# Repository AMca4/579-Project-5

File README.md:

# EE579 ADVANCED MICROCONTROLLER PROJECT
## General project instructions and objectives
The following is essentially what we wrre tasked to do.

Build a vehicle capable of playing a game of skittles in the corridor outside RC6.41.
Two teams' vehicles will compete simultaneously, with a single set of 2 black metal “skittles” placed between 6 and 10 metres from both vehicles, and both vehicles beginning adjacent to each other. The skittles will consist of two tin soup cans soldered end to end and painted.

You will be given a model car to modify. You are expected to retro-fit this vehicle to operate autonomously, without altering the chassis (in particular, the wheel positions or bearings) or the drive train of the vehicle. Teams will be given two runs, alongside another vehicle. Runs will be 2 minutes long. During the heat, no team member will be permitted beyond the start line. Teams will score the number of complete seconds until they knock over the skittle, or two minutes per skittle if they do not knock over the skittle. The object is to get the lowest score in a round, and the lowest score from the two rounds will be counted. The top four teams will compete in a semi-final and the final two in the final.

In addition to two black skittles there will be a white skittle. Knocking over the white skittle will result in disqualification from the round.
+ Teams will see the position of the skittles one minute prior to the start of a round.
- The vehicle must operate autonomously. No external control may be given to the vehicle after it has been started.
- For the purposes of adjudicating a tie, the vehicle displacement from the start line at the end of the round will be measured, with longer distances scoring higher.

Marks for the project will be calculated on a group basis. The design and construction of the device will be marked out of 300. The team scoring the shortest time (or greatest displacement, should no team finish), will be given at additional 30 bonus marks. The group coming second will get 15 additional marks.

The design is unconstrained, except that your design may not run a general purpose operating system, such as Linux. Passive components can be requested from the workshop. Other components may be requested but a case may need to be made.

A Technical Documentation File must be produced for the design. This file must include:
- The specification of the design.
- Description of the hardware including circuit diagram and test points/instructions.
- Description of the software including a functional description.
- Usage instructions

The TDF is not a description of the construction of the project, but a description of the end product. A key assessment criteria of the TDF will be how easy it would be, using the TDF, to make a modification or extension to the design. It is expected that the TDF will be in the order of 25 to 30 pages, including diagrams.

In addition to the Technical Document File, a Policies and Procedures Document (PPD) must be produced documenting your group working practices, and in particular code versioning and review, and also measures taken during the design and construction phase to increase resilience to delays due to illness or other unforeseen circumstances. The PPD is expected to be in the order of one or two pages.

A descriptive report on the project is not required. However, the log books of each project member must be returned with the Technical Documentation File and it is expected that these log books will describe the design and debugging process.

By default, the group mark will be divided equally between all group members. However, group members may ask for a different proportional assignment of marks between group members at the time the project is submitted. It is up to group members themselves to make decisions regarding which group member should undertake which part of the design. The project is to be demonstrated during the exam diet. The Technical Documentation File must be submitted on or before the Monday of the week following the demo. The mark allocated to each student will be considered to be a percentage, 70% of which will go towards the final course mark. The remaining 30% of the final mark will come from the log book and assignments.

Room RC6.23 is allocated to the class on Friday for constructing and testing the hardware. Safety regulations require that more than one person be present in the room when any work is carried out - attending as a group satisfies this requirement.
## Setup instructions
We have used VS code for building this project. The following are the instructions for setting up the environment, if you wish to alter the code and flash it to the ESP32.
### Windows setup:
- Step 1: Download the latest version of [Python](https://www.python.org/downloads/) and [Git](https://git-scm.com/download/win) 
- Step 2: Download Espressif's Toolchain [here](https://docs.espressif.com/projects/esp-idf/en/latest/esp32/get-started/windows-setup.html).
- Step 3: Make sure to open the installer with administrator rights. On the third screen, ***don't click on next before the scanning is complete!***. If there are no warnings you may procceed to the next step by clicking next. If you notice warnings, click on apply fixes and grant administrator rights on the pop-up screen. You may then proceed to the next step by clicking on next.
- Step 4: You may select to Download ESP-IDF or Use an existing ESP-IDF directory if you already have an installation on the ESP-IDF Tools.
- Step 5: ***This is a very crucial step!*** Make sure you make a note of the directory it wants to install to and select any of the above. Our recommendation is to select the latest release from (release branch - git clone).
- Step 6: Specify where you would like the ESP-IDF Tools to be installed and **make a note of it!**
- Step 7: You may select any of the options but we recommend you go for the full installation, always making sure to select the appropriate drivers for your own board.
- Step 8: In the *Ready to Install* screen verify all your choices by clicking Install. At this stage it's good to once more make a note of the location for the *ESP-IDF* and the *IDF_TOOLS_PATH*.
- Step 9: You'll now get a couple of pop-ups for granting administrator rights and another one for installing the drivers. Make sure to grant all of these. You can now let the installer download and install the ESP-IDF.
- Step 10: Download [VS code](https://code.visualstudio.com/download) and install using the default options.
- Step 11: Once the setup is complete, open VS code and click on Crtl+Shift+X navigate to the extentions tab. You can also find it on the left hand-side of VS Code. In the search bar type in ESP-IDF and install it.
- Step 12: You can now press Crtl+Shift+P (or navigate to the top of VS code and click on the search bar & click on *Show and Run Commands*) and type in *Configure ESP-IDF Extention*. Give it a second to load and then you'll be greeted with a welcome screen.
- Step 13: Choose *USE EXISTING SETUP* and then your installation should appear. Clicking on it, will install the necessary libraries for VS code to communicate with the ESP-IDF tools and once instructed you may close the window. You can skip to step 15.
- Step 14: If your installation doesn't appear, choose *Search ESP-IDF in system* and select the download server (*github if you followed our instructions above*) and *Find ESP-IDF in your system* from the dropdown. Now specify the locations for the *ESP-IDF* and the *IDF_TOOLS_PATH* from step 8 and click on install. Wait for it to finish and once instructed you may close the window.
- Step 15: Congratulations! You have successfully set-up *ESP-IDF* in your system!

### MacOS Setup:
- Follow the steps listed [here](https://docs.espressif.com/projects/esp-idf/en/stable/esp32/get-started/linux-macos-setup.html).

### Linux Setup:
- Follow the steps listed [here](https://docs.espressif.com/projects/esp-idf/en/stable/esp32/get-started/linux-macos-setup.html).

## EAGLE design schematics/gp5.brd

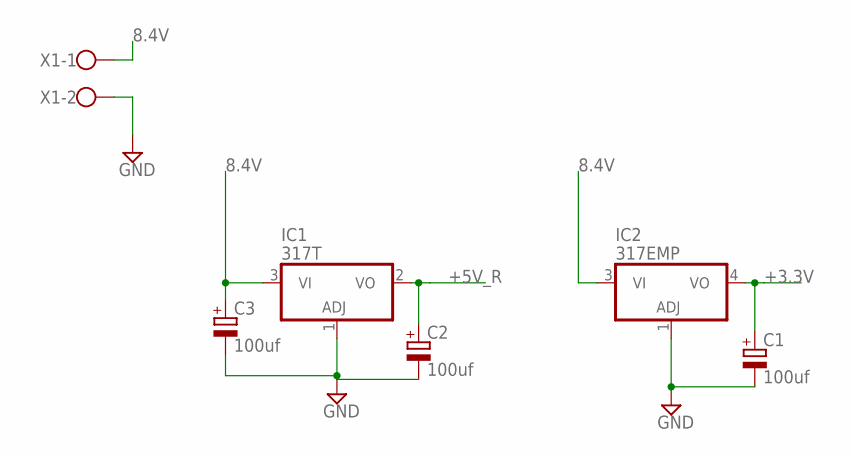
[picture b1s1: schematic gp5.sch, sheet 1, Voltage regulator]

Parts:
C1, C2, C3: 100uf; B45181B
IC1: 317T; TO220H
IC2: 317EMP; SOT223
X1: W237-102

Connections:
8.4V: C3.+, IC1.3 (VI), IC2.3 (VI), X1.1
+3.3V: C1.+, IC2.4 (VO); also elsewhere on the board
+5V_R: C2.+, IC1.2 (VO); also elsewhere on the board
GND: C1.-, C2.-, C3.-, IC1.1 (ADJ), IC2.1 (ADJ), X1.2; also elsewhere on the board

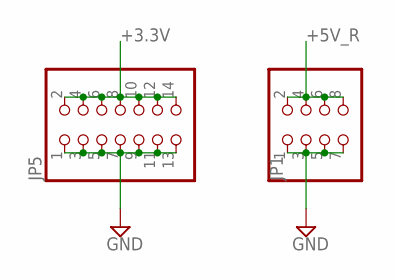
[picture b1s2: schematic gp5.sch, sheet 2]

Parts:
JP1: PINHD-2X4; 2X04
JP5: PINHD-2X7; 2X07

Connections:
+3.3V: JP5.2, JP5.4, JP5.6, JP5.8, JP5.10, JP5.12, JP5.14; also elsewhere on the board
+5V_R: JP1.2, JP1.4, JP1.6, JP1.8; also elsewhere on the board
GND: JP1.1, JP1.3, JP1.5, JP1.7, JP5.1, JP5.3, JP5.5, JP5.7, JP5.9, JP5.11, JP5.13; also elsewhere on the board

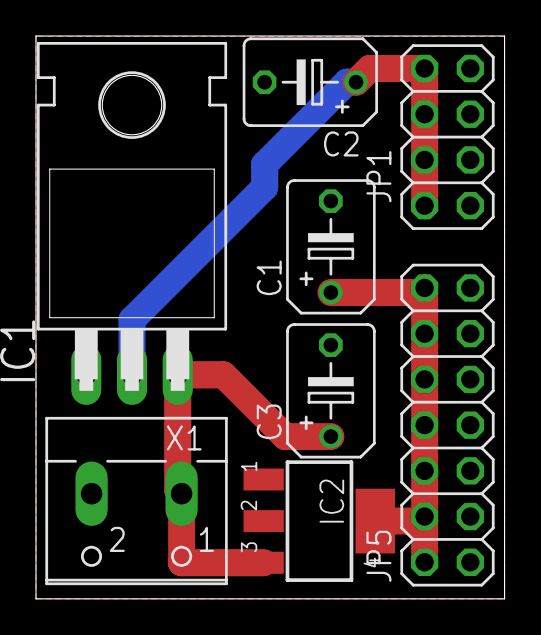
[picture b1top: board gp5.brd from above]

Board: 2 copper layers, 26.0 x 31.3 mm, 8 parts (0 on the bottom side), 4 nets.

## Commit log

2024-01-17 Update README.md
    Update READMe
2024-01-17 Update README.md
    Restructured READMe file
2024-01-25 Added .gitignore file
2024-01-27 Update README.md to include windows setup instructions
2024-01-27 Update README.md to use bullet points.
2024-01-29 Update README.md to include general instructions and objectives.
2024-01-29 Update README.md to fix bullet points
2024-01-29 Update README.md to finally fix the bullet points
2024-01-31 Delete skittles_project.code-workspace
    will re-upload
2024-01-31 Delete skittles.code.code-workspace
    will re-upload
2024-01-31 re-upload finalised ultrasonic code
2024-02-06 Putting the ultrasonic code into a folder
2024-02-06 Putting the ultrasonic folder up
2024-02-06 Update README.md to include the win setup instructions
2024-02-07 Changed the AP name and deleted 2 unecessary includes
2024-02-08 Add files via upload
    PCB EAGLE Design for 2 IR Sensors as-well as a 9-5V Converter.
2024-02-10 Add files via upload
    Reads Voltage from IR sensor output, controls Servo direction based off of IR voltage output readings.
2024-02-11 Working web server with multipple URIs
2024-02-12 Webserver Running with multiple pages and able to kill and restart
2024-02-13 Webpage URI's updated to be clearer
2024-02-13 Started Updating code to websocket server instead of http server
2024-02-13 Add files via upload
    make sure to add the "build" folder aswell as these
2024-02-15 Telemetry updataed to use webserve socket
2024-02-22 Added accelerometer non-working file & git ignore file
2024-02-28 initial commit of radar and accelerometer. accelerometer at 50% complete but untested
2024-02-29 Initial upload of data collection
2024-03-29 Restructured folders and dirs for the measurement algo
2024-03-30 Start of master algorithm coding with measurements function
2024-03-30 Delete master_algorithm/build directory
    No need for the build/ directory
2024-03-30 Changed sensor data to struct for easier handling
2024-03-31 created the accelerometer as interrupt and added it to master algo
2024-03-31 board schematics upload
2024-04-04 temp save
2024-04-05 Add files via upload
    Basic State Flow main (Incomplete just for reference)
2024-04-06 sync across devices
2024-04-07 finalised schematic files
2024-04-07 skematikoooooo
2024-04-09 final power board schematic
2024-04-09 tidying up develop branch
2024-04-09 cleanup remote not local
2024-04-10 adding kinematics functions
2024-04-11 Add files via upload
    Servo code updated (split into .h and .c constituents)
2024-04-12 Ignore no code inside
2024-04-12 minor tweak in conditional stmts
2024-04-13 done with the kinematics, still needs calibration
2024-04-16 kinematics finalisation
2024-04-16 finalising kinematics
2024-04-18 Adding master Alg
2024-04-23 testing the servo code to try and calibrate
2024-04-23 APDS COlour Sensor Main
2024-04-23 temp sync save
2024-04-24 progress on multi
2024-04-24 temp servo save
2024-04-26 i2c on multi advancements
2024-04-29 speed and bin file optimisations
2024-04-30 i2c testing 2 colors working together
2024-05-01 "partition table error fixed"
2024-05-01 don't remember what i changed
2024-05-01 upload i2c comps
2024-05-01 fixed naming conventions and neeted the tof files
2024-05-01 pins updated
2024-05-01 ssid name updated
2024-05-01 fix scl and sda definitions in tof
2024-05-01 fixed misc errors
2024-05-01 turning fixed
2024-05-02 changes to main
2024-05-02 test kinematics added
2024-05-02 accelerometer comment out
2024-05-02 removede accelerometer defines
2024-05-02 accelerometer header file made
2024-05-02 cmake change to remove accelerometer
2024-05-02 accelerometer header file fix
2024-05-02 renamed main_app to app_main
2024-05-02 added includes in i2c_top_level header
2024-05-02 fixed includes
2024-05-02 more include fixes
2024-05-02 fixed def errors
2024-05-02 cmake error make
2024-05-02 working webserver and ap with start flags
2024-05-02 switched back to using taskcreate
2024-05-02 ultrasonic pins updated
2024-05-02 don't know
2024-05-02 change sonic code and try to debug errors
2024-05-02 backup the previous master_algorithm
2024-05-02 new program to test the sonic
2024-05-02 newVersionMasterAlgo
2024-05-02 WORKING CODE
2024-05-07 Add files via upload
    updated final algorithm
2024-05-09 add .stl files
2024-05-09 add assembly videos
2024-05-10 Add files via upload
    Testing files for apds9960 sensor
2024-05-10 Add files via upload
    webserver old telemetry version
2024-05-10 Add files via upload
    new webserver
2024-05-10 Add files via upload
    tof code running
2024-05-10 Add files via upload
    some sensor debugging code/developing code added
2024-05-10 Add files via upload
    i2c debugging
